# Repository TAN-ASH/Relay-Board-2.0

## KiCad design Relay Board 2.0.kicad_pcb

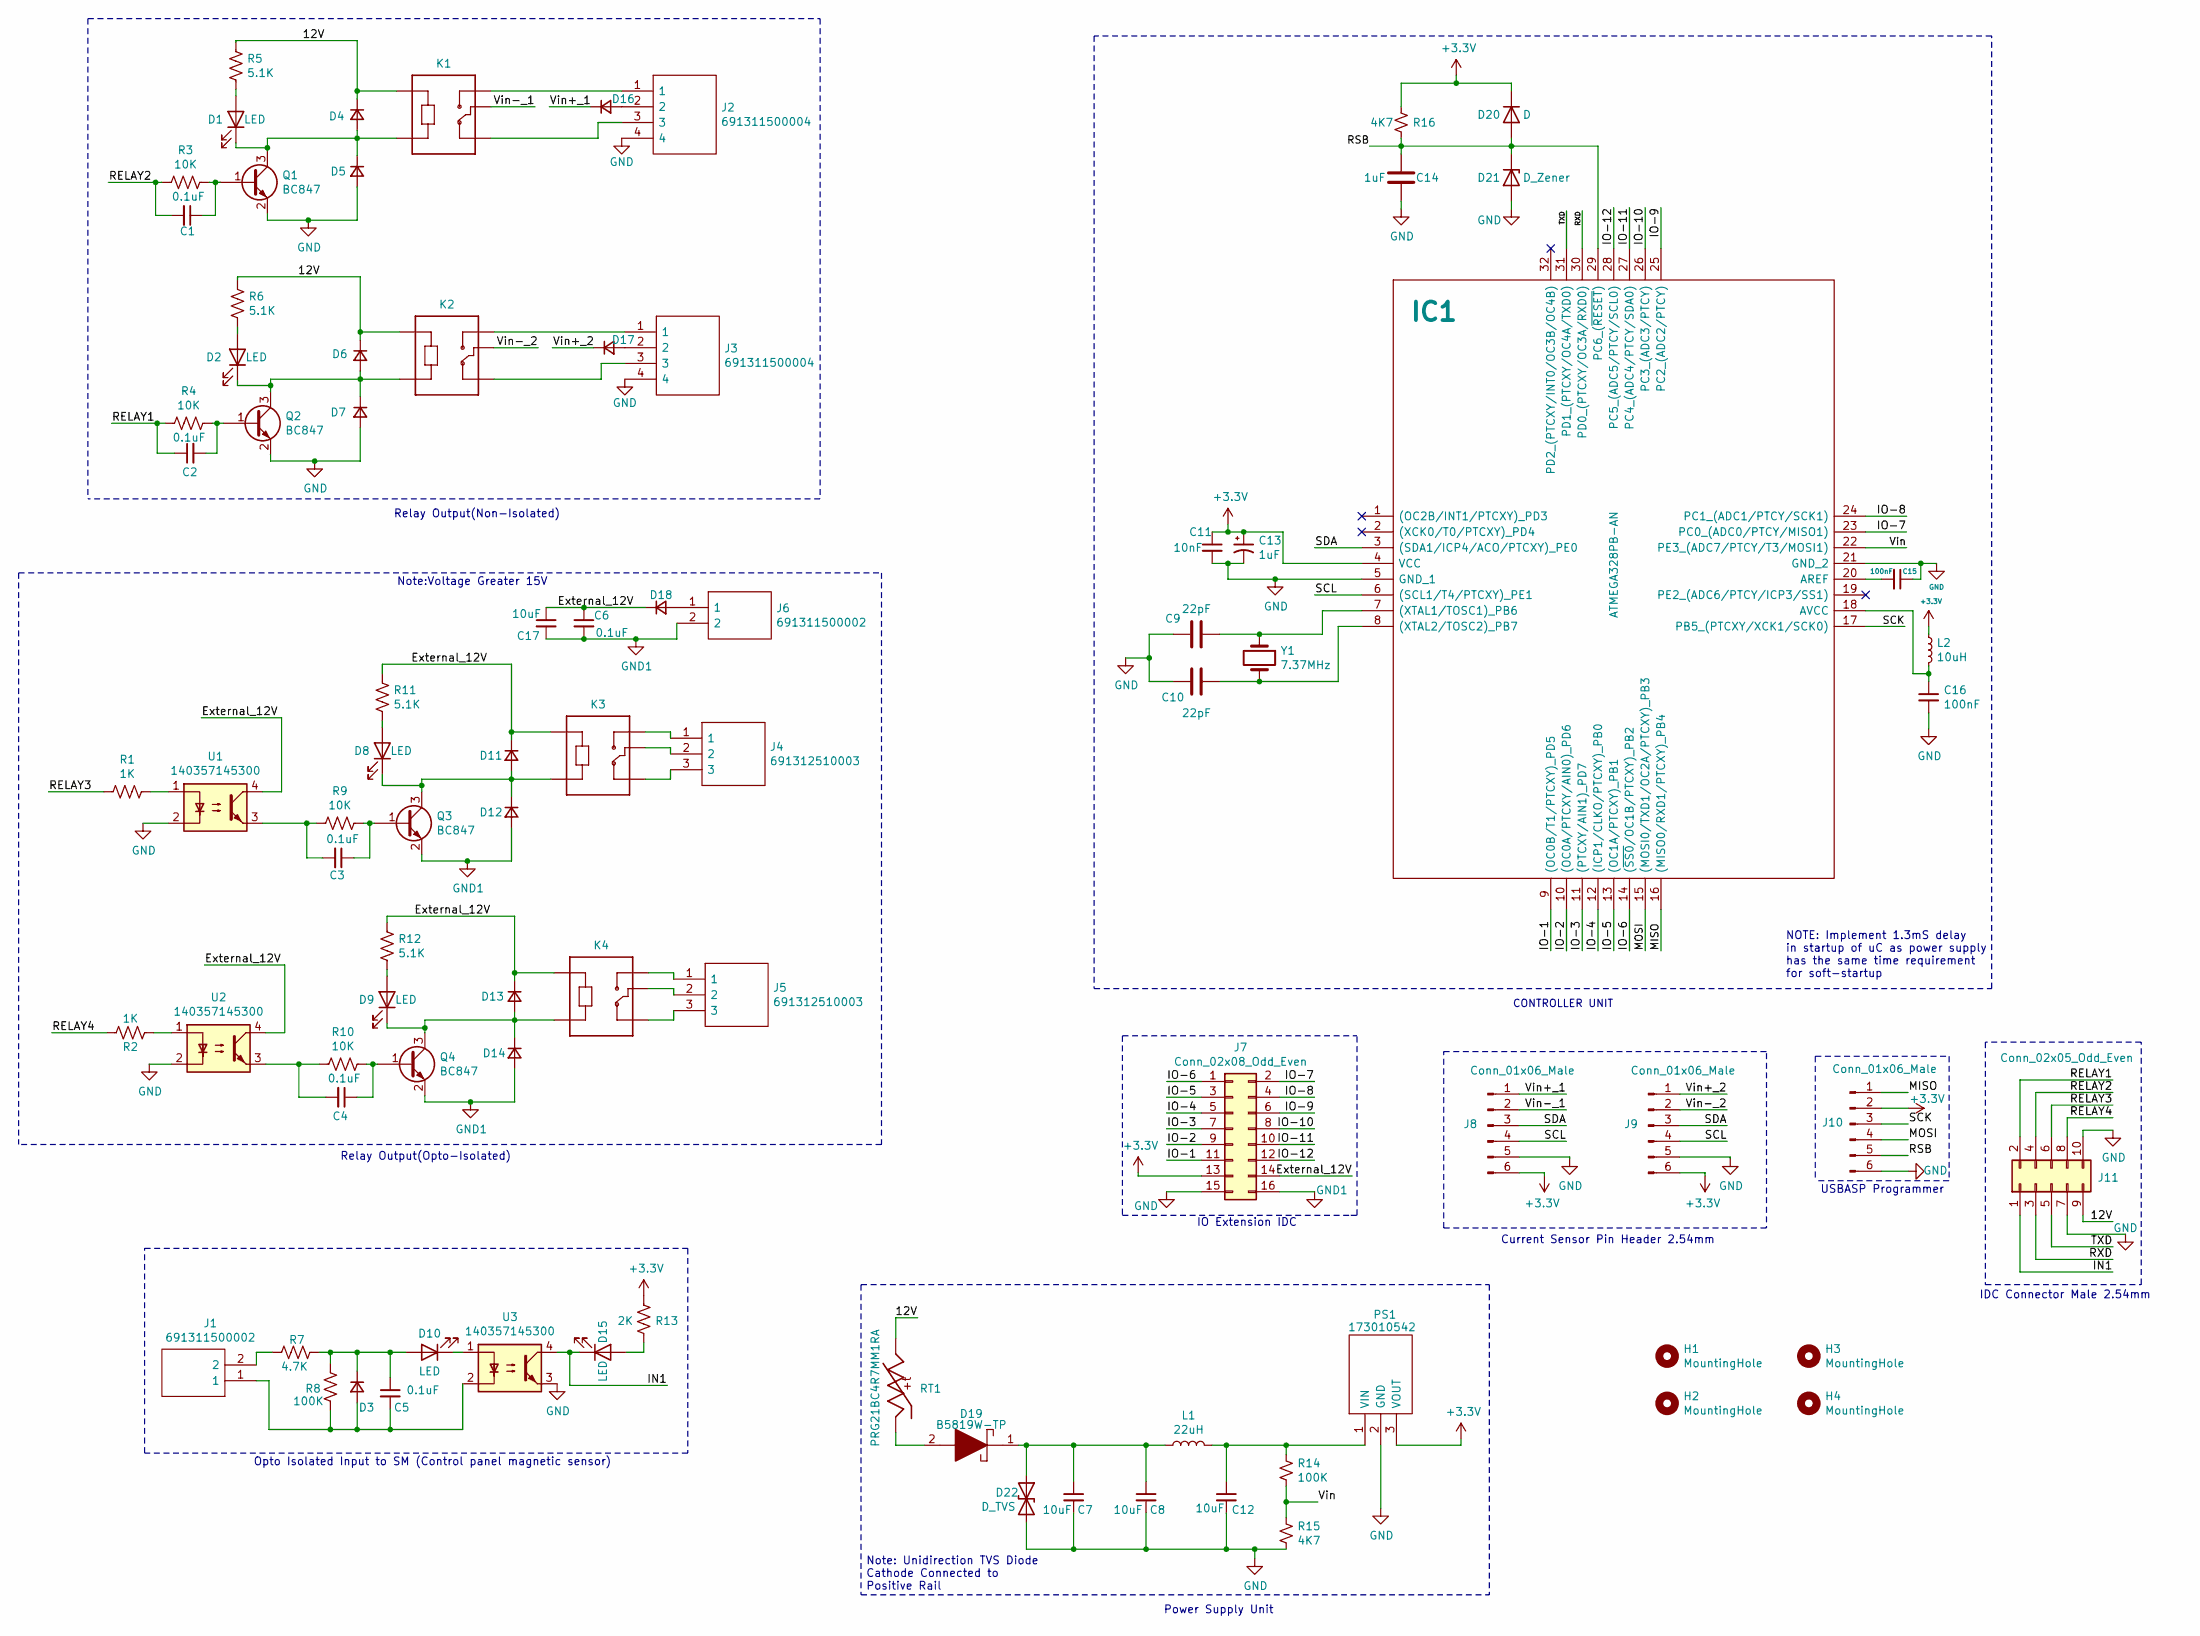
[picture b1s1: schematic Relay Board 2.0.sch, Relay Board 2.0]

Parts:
C1, C2, C3, C4, C5, C6: 0.1uF; C_0603_1608Metric
C7, C8, C12: 10uF; C_0805_2012Metric
C9, C10: 22pF; C_0603_1608Metric
C11: 10nF; C_0603_1608Metric
C13: 1uF; C_1206_3216Metric
C14: 1uF; C_0603_1608Metric
C15, C16: 100nF; C_0603_1608Metric
C17: 10uF; CP_EIA-3528-12_Kemet-T
D1, D2, D8, D9, D10, D15: LED; LED_0805_2012Metric
D3, D4, D5, D6, D7, D11, D12, D13, D14: D_Small; FDLL4448
D16, D17, D18: D_Small; SOD3716X135N
D19: B5819W-TP; SOD3716X135N; Manufacturer_Part_Number B5819W-TP; Mouser Part Number 833-B5819W-TP
D20: D; FDLL4448
D21: D_Zener; SOD3716X145N
D22: D_TVS; D_SOD-123
H1, H2, H3, H4: MountingHole; MountingHole_2.2mm_M2_ISO7380_Pad
IC1: ATMEGA328PB-AN; QFP80P900X900X120-32N; Manufacturer_Part_Number ATMEGA328PB-AN; Mouser Part Number 556-ATMEGA328PB-AN
J1, J6: 691311500002; Manufacturer_Part_Number 691311500002; Mouser Part Number 710-691311500002
J2, J3: 691311500004; Manufacturer_Part_Number 691311500004; Mouser Part Number 710-691311500004
J4, J5: 691312510003; 691311500003; Manufacturer_Part_Number 691312510003; Mouser Part Number 710-691312510003
J7: Conn_02x08_Odd_Even; IDC-Header_2x08_P2.54mm_Vertical
J8, J9, J10: Conn_01x06_Male; PinHeader_1x06_P2.54mm_Vertical
J11: Conn_02x05_Odd_Even; IDC-Header_2x05_P2.54mm_Vertical
K1, K2, K3, K4: SRD-05VDC-SL-C; RELAY_SRD-05VDC-SL-C
L1: 22uH; WE-PD2_5848_582055
L2: 10uH; L_1206_3216Metric
PS1: 173010542; Manufacturer_Part_Number 173010542; Mouser Part Number 710-173010542
Q1, Q2, Q3, Q4: BC847; SOT-23
R1, R2: 1K; R_0603_1608Metric
R3, R4, R9, R10: 10K; R_0603_1608Metric
R5, R6, R11, R12: 5.1K; R_0603_1608Metric
R7: 4.7K; R_0603_1608Metric
R8, R14: 100K; R_0603_1608Metric
R13: 2K; R_0603_1608Metric
R15, R16: 4K7; R_0603_1608Metric
RT1: PRG21BC4R7MM1RA; THRMC2012X110N; PARTREV N/A
U1, U2, U3: 140357145300; SOP254P700X210-4N
Y1: 7.37MHz; ABLS373728MHZD4YT

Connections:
+3V3: C11.1, C13.1, D20.1 (K), IC1.4 (VCC), J7.13, J8.6, J9.6, J10.2, L2.1, PS1.3 (VOUT), R13.2, R16.1
/12V: D4.1 (K), D6.1 (K), J11.9, K1.A1, K2.A1, R5.2, R6.2, RT1.2
/External_12V: C6.1, C17.1, D11.1 (K), D13.1 (K), D18.1 (K), J7.14, K3.A1, K4.A1, R11.2, R12.2, U1.4, U2.4
/IN1: D15.1 (K), J11.1, U3.4
/IO-1: IC1.9 ((OC0B/T1/PTCXY)_PD5), J7.11
/IO-2: IC1.10 ((OC0A/PTCXY/AIN0)_PD6), J7.9
/IO-3: IC1.11 ((PTCXY/AIN1)_PD7), J7.7
/IO-4: IC1.12 ((ICP1/CLKO/PTCXY)_PB0), J7.5
/IO-5: IC1.13 ((OC1A/PTCXY)_PB1), J7.3
/IO-6: IC1.14 ((~SS0~/OC1B/PTCXY)_PB2), J7.1
/IO-7: IC1.23 (PC0_(ADC0/PTCY/MISO1)), J7.2
/IO-8: IC1.24 (PC1_(ADC1/PTCY/SCK1)), J7.4
/IO-9: IC1.25 (PC2_(ADC2/PTCY)), J7.6
/IO-10: IC1.26 (PC3_(ADC3/PTCY)), J7.8
/IO-11: IC1.27 (PC4_(ADC4/PTCY/SDA0)), J7.10
/IO-12: IC1.28 (PC5_(ADC5/PTCY/SCL0)), J7.12
/MISO: IC1.16 ((MISO0/RXD1/PTCXY)_PB4), J10.1
/MOSI: IC1.15 ((MOSI0/TXD1/OC2A/PTCXY)_PB3), J10.4
/RELAY1: C2.1, J11.2, R4.1
/RELAY2: C1.2, J11.4, R3.1
/RELAY3: J11.6, R1.1
/RELAY4: J11.8, R2.1
/RSB: C14.1, D20.2 (A), D21.1 (K), IC1.29 (PC6_(~RESET)), J10.5, R16.2
/RXD: IC1.30 (PD0_(PTCXY/OC3A/RXD0)), J11.3
/SCK: IC1.17 (PB5_(PTCXY/XCK1/SCK0)), J10.3
/SCL: IC1.6 ((SCL1/T4/PTCXY)_PE1), J8.4, J9.4
/SDA: IC1.3 ((SDA1/ICP4/ACO/PTCXY)_PE0), J8.3, J9.3
/TXD: IC1.31 (PD1_(PTCXY/OC4A/TXD0)), J11.5
/Vin: IC1.22 (PE3_(ADC7/PTCY/T3/MOSI1)), R14.2, R15.1
/Vin+_1: D16.1 (K), J8.1
/Vin+_2: D17.1 (K), J9.1
/Vin-_1: J8.2, K1.COM
/Vin-_2: J9.2, K2.COM
GND: C7.2, C8.2, C9.2, C10.2, C11.2, C12.2, C13.2, C14.2, C15.1, C16.2, D5.2 (A), D7.2 (A), D21.2 (A), D22.2 (A2), IC1.5 (GND_1), IC1.21 (GND_2), J2.4, J3.4, J7.15, J8.5, J9.5, J10.6, J11.7, J11.10, PS1.2 (GND), Q1.2 (E), Q2.2 (E), R15.2, U1.2, U2.2, U3.3
GND1: C6.2, C17.2, D12.2 (A), D14.2 (A), J6.2, J7.16, Q3.2 (E), Q4.2 (E)
unnamed: C1.1, Q1.1 (B), R3.2
unnamed: C2.2, Q2.1 (B), R4.2
unnamed: C3.1, Q3.1 (B), R9.2
unnamed: C3.2, R9.1, U1.3
unnamed: C4.1, Q4.1 (B), R10.2
unnamed: C4.2, R10.1, U2.3
unnamed: C5.1, D3.1 (K), D10.2 (A), R7.1, R8.1
unnamed: C5.2, D3.2 (A), J1.1, R8.2, U3.2
unnamed: C7.1, C8.1, D19.1, D22.1 (A1), L1.1
unnamed: C9.1, IC1.7 ((XTAL1/TOSC1)_PB6), Y1.1
unnamed: C10.1, IC1.8 ((XTAL2/TOSC2)_PB7), Y1.2
unnamed: C12.1, L1.2, PS1.1 (VIN), R14.1
unnamed: C15.2, IC1.20 (AREF)
unnamed: C16.1, IC1.18 (AVCC), L2.2
unnamed: D1.1 (K), D4.2 (A), D5.1 (K), K1.A2, Q1.3 (C)
unnamed: D1.2 (A), R5.1
unnamed: D2.1 (K), D6.2 (A), D7.1 (K), K2.A2, Q2.3 (C)
unnamed: D2.2 (A), R6.1
unnamed: D8.2 (A), R11.1
unnamed: D9.2 (A), R12.1
unnamed: D10.1 (K), U3.1
unnamed: D8.1 (K), D11.2 (A), D12.1 (K), K3.A2, Q3.3 (C)
unnamed: D9.1 (K), D13.2 (A), D14.1 (K), K4.A2, Q4.3 (C)
unnamed: D15.2 (A), R13.1
unnamed: D16.2 (A), J2.2
unnamed: D17.2 (A), J3.2
unnamed: D18.2 (A), J6.1
unnamed: D19.2, RT1.1
unnamed: J1.2, R7.2
unnamed: J2.1, K1.NO
unnamed: J2.3, K1.NC
unnamed: J3.1, K2.NO
unnamed: J3.3, K2.NC
unnamed: J4.1, K3.NO
unnamed: J4.2, K3.COM
unnamed: J4.3, K3.NC
unnamed: J5.1, K4.NO
unnamed: J5.2, K4.COM
unnamed: J5.3, K4.NC
unnamed: R1.2, U1.1
unnamed: R2.2, U2.1

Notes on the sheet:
CONTROLLER UNIT
USBASP Programmer
IDC Connector Male 2.54mm
Power Supply Unit
Current Sensor Pin Header 2.54mm
Relay Output(Opto-Isolated)
Relay Output(Non-Isolated)
IO Extension IDC
Opto Isolated Input to SM (Control panel magnetic sensor)
NOTE: Implement 1.3mS delay in startup of uC as power supply has the same time requirement for soft-startup
Note:Voltage Greater 15V
Note: Unidirection TVS Diode Cathode Connected to Positive Rail

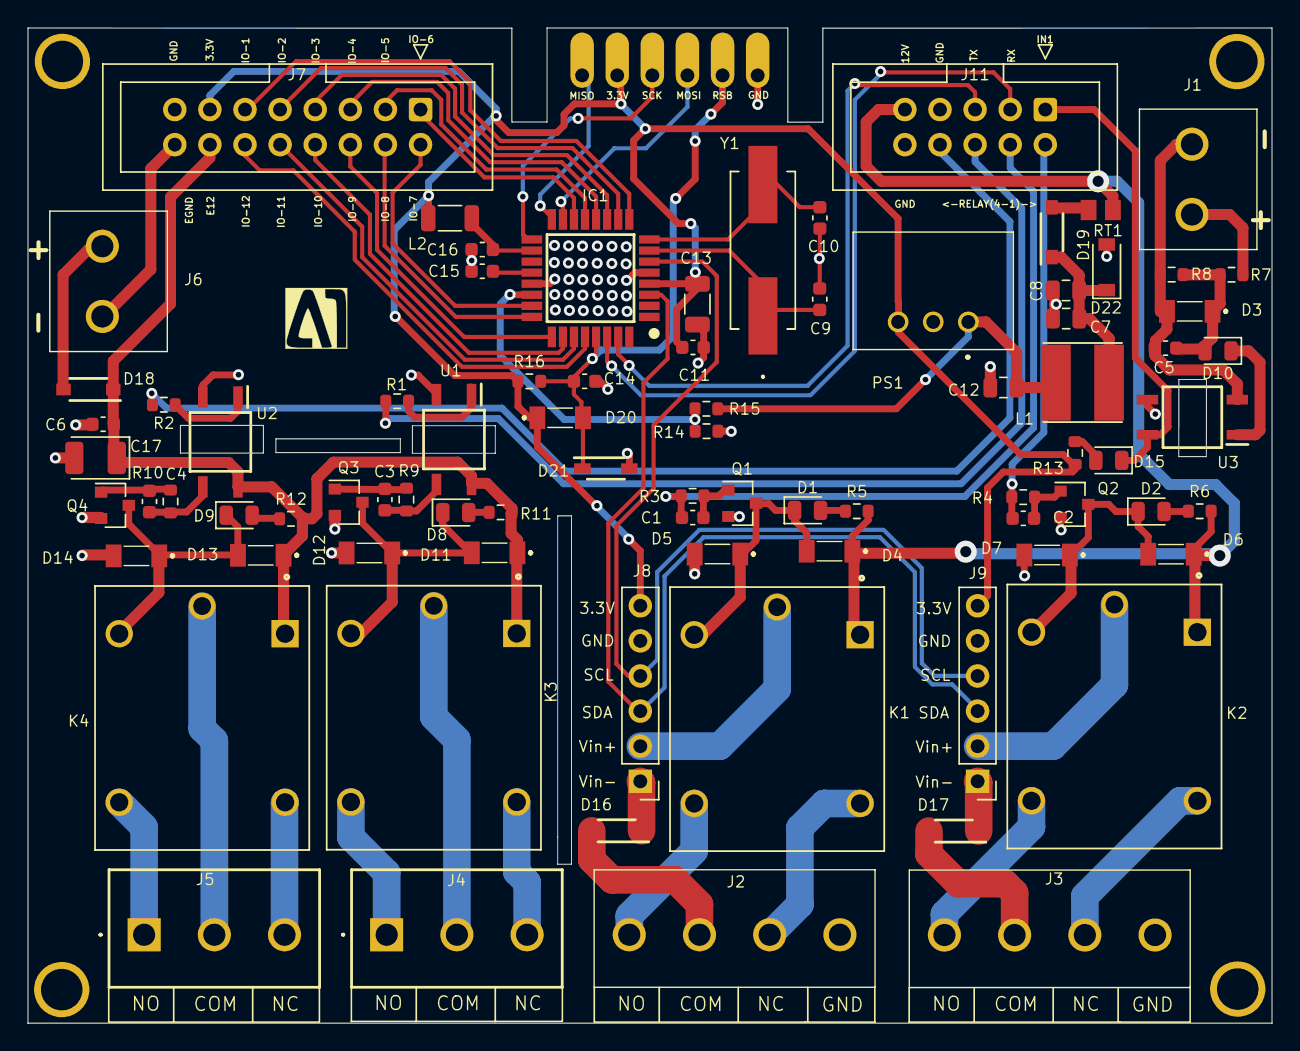
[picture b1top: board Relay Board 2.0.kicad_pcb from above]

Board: 2 copper layers, 90.0 x 72.0 mm, 87 parts (0 on the bottom side), 76 nets.

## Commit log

2021-12-04 Relay Board 2.0
